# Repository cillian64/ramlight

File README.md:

# ramlight
Dummy DDR4 DIMM with LEDs and controller

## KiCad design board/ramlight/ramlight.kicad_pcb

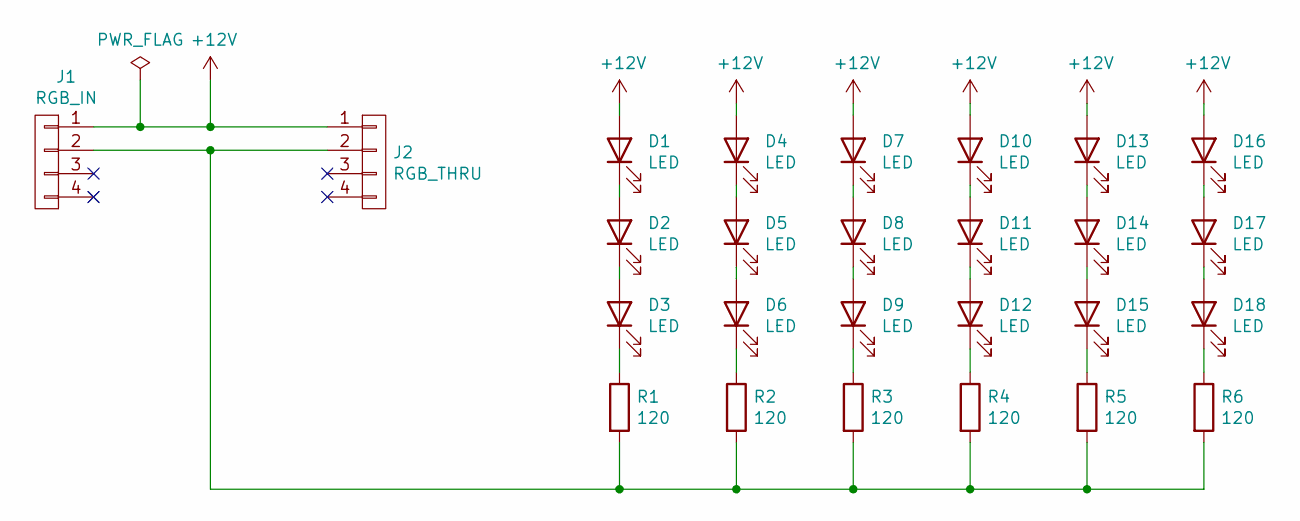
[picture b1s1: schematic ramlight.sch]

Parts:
D1, D2, D3, D4, D5, D6, D7, D8, D9, D10, D11, D12, D13, D14, D15, D16, D17, D18: LED; OVS_2101
J1: RGB_IN; Molex_KK-6410-04_04x2.54mm_Straight
J2: RGB_THRU; Molex_KK-6410-04_04x2.54mm_Straight
R1, R2, R3, R4, R5, R6: 120; R_1206_HandSoldering

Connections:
+12V: D1.2 (A), D4.2 (A), D7.2 (A), D10.2 (A), D13.2 (A), D16.2 (A), J1.1, J2.1
unnamed: D1.1 (K), D2.2 (A)
unnamed: D2.1 (K), D3.2 (A)
unnamed: D3.1 (K), R1.1
unnamed: D4.1 (K), D5.2 (A)
unnamed: D5.1 (K), D6.2 (A)
unnamed: D6.1 (K), R2.1
unnamed: D7.1 (K), D8.2 (A)
unnamed: D8.1 (K), D9.2 (A)
unnamed: D9.1 (K), R3.1
unnamed: D10.1 (K), D11.2 (A)
unnamed: D11.1 (K), D12.2 (A)
unnamed: D12.1 (K), R4.1
unnamed: D13.1 (K), D14.2 (A)
unnamed: D14.1 (K), D15.2 (A)
unnamed: D15.1 (K), R5.1
unnamed: D16.1 (K), D17.2 (A)
unnamed: D17.1 (K), D18.2 (A)
unnamed: D18.1 (K), R6.1
unnamed: J1.2, J2.2, R1.2, R2.2, R3.2, R4.2, R5.2, R6.2

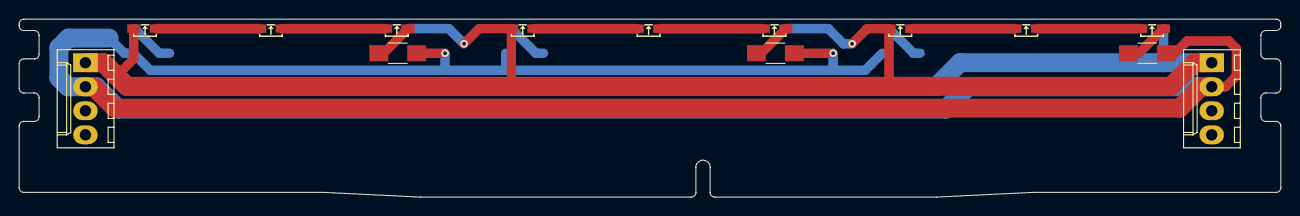
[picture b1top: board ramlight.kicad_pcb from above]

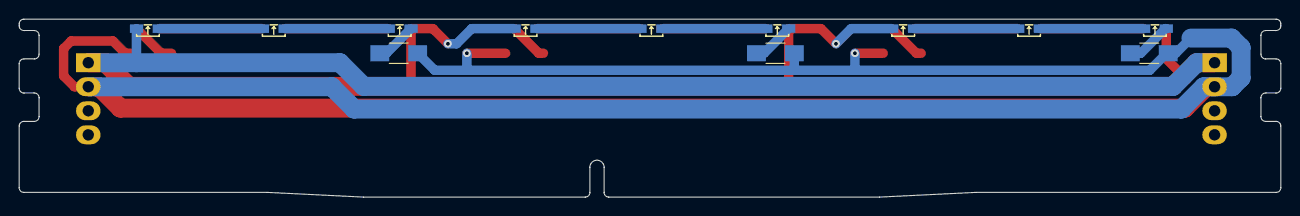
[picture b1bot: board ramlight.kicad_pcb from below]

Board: 2 copper layers, 133.3 x 18.8 mm, 26 parts (12 on the bottom side), 20 nets.

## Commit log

2020-09-19 Rough draft of schematic and PCB
